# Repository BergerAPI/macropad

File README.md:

# Macropad

This project demonstrates how to build a simple macropad powered by a microcontroller using the same chip as the Raspberry Pi Pico (RP2040).
You can use the files here to 3D print, assemble, and program your own version!

The video of the project was recorded using a custom microcontroller, which is not yet publicly available.
However, you can safely use a Raspberry Pi Pico instead — it uses the same RP2040 chip, so all firmware and pinouts should work with minimal or no changes.

## 3D Model Notice

The included 3D model files are provided as-is.
Before printing, you must adjust them to include proper tolerances (fit clearance) for your printer and switches — otherwise, parts may fit too tightly or loosely.

## Requirements

- Microcontroller: Raspberry Pi Pico (or basically any microcontroller)
- Firmware: Included in this repository
- Switches & Keycaps: Any standard mechanical key switches
- 3D Printer: To print the enclosure and plate (or just order the parts like I did)

Optional:

- EEPROM chip — required for advanced features like changing macros on the fly like with QMK

⚠️ Note: The Raspberry Pi Pico does not have built-in EEPROM, so this functionality will be unavailable unless you add one externally.

## Getting Started 🚀

- Print the enclosure and plate (remember to add tolerances).
Assemble the hardware.
- Flash the firmware to your Pico (instructions in /firmware).
- Connect to your computer and enjoy your new macropad!

## Open Licence
Feel free to play with the provided files and change them to your liking - I even encourage it.

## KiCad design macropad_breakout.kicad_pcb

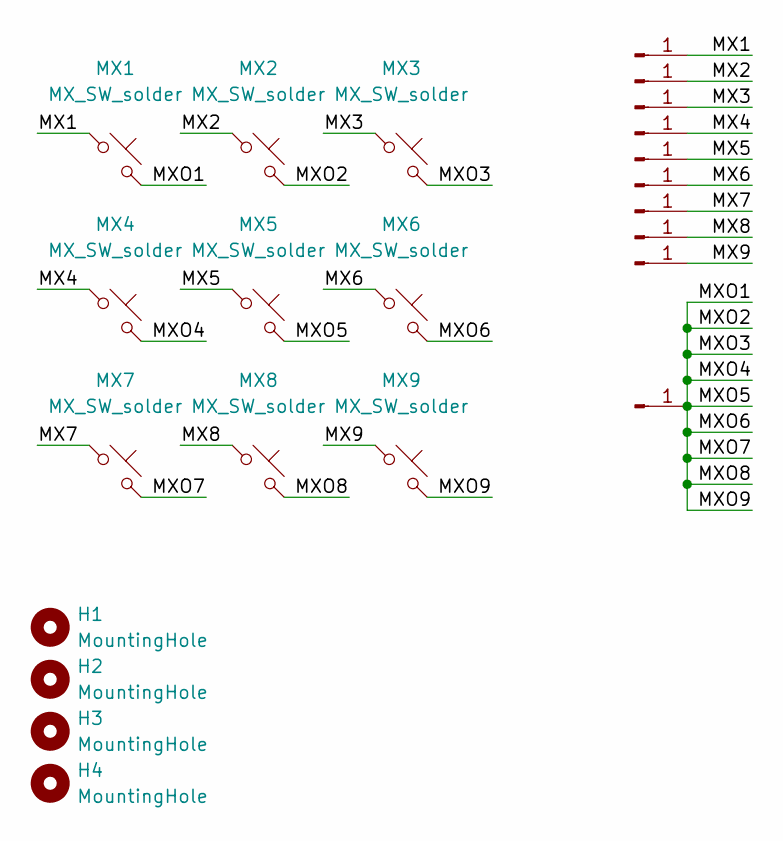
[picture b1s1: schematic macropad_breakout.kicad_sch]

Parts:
H1, H2, H3, H4: MountingHole; MountingHole_3mm
J1, J2, J3, J4, J5, J6, J7, J8, J9, J10: Conn_01x01_Pin; TestPoint_Pad_4.0x4.0mm
MX1, MX2, MX3, MX4, MX5, MX6, MX7, MX8, MX9: MX_SW_solder; SW_MX_1u

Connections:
/MX1: J1.1, MX1.1
/MX2: J2.1, MX2.1
/MX3: J3.1, MX3.1
/MX4: J4.1, MX4.1
/MX5: J5.1, MX5.1
/MX6: J6.1, MX6.1
/MX7: J7.1, MX7.1
/MX8: J8.1, MX8.1
/MX9: J9.1, MX9.1
/MXO1: J10.1, MX1.2, MX2.2, MX3.2, MX4.2, MX5.2, MX6.2, MX7.2, MX8.2, MX9.2

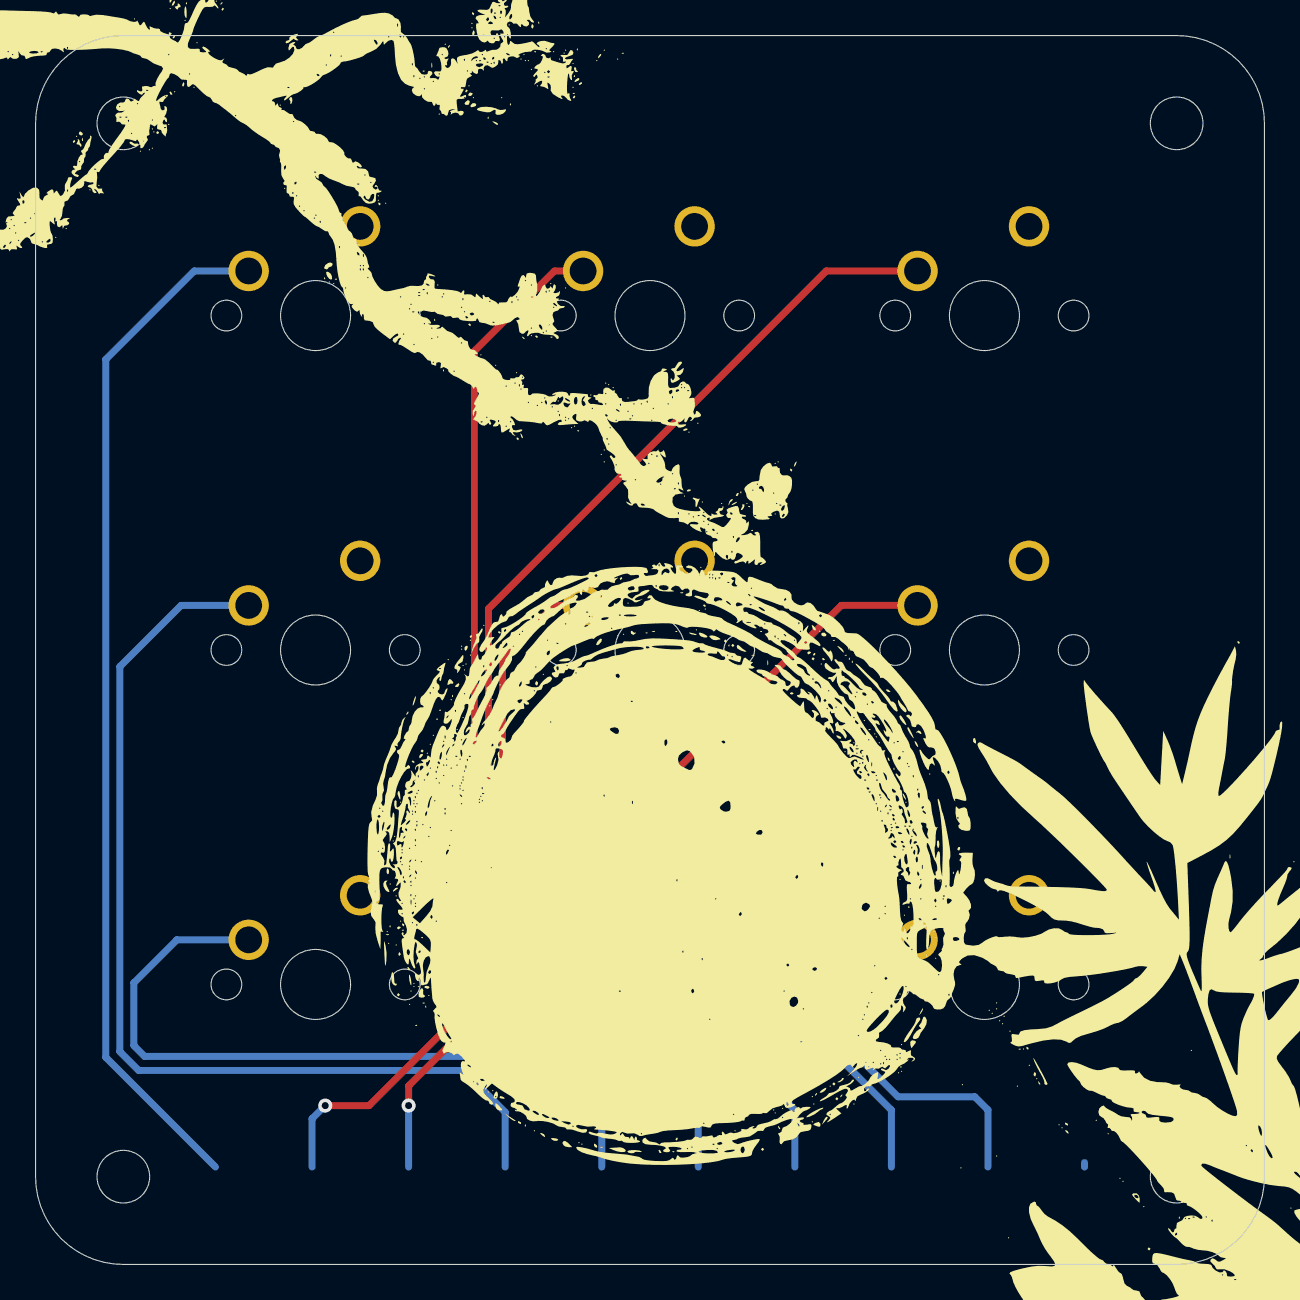
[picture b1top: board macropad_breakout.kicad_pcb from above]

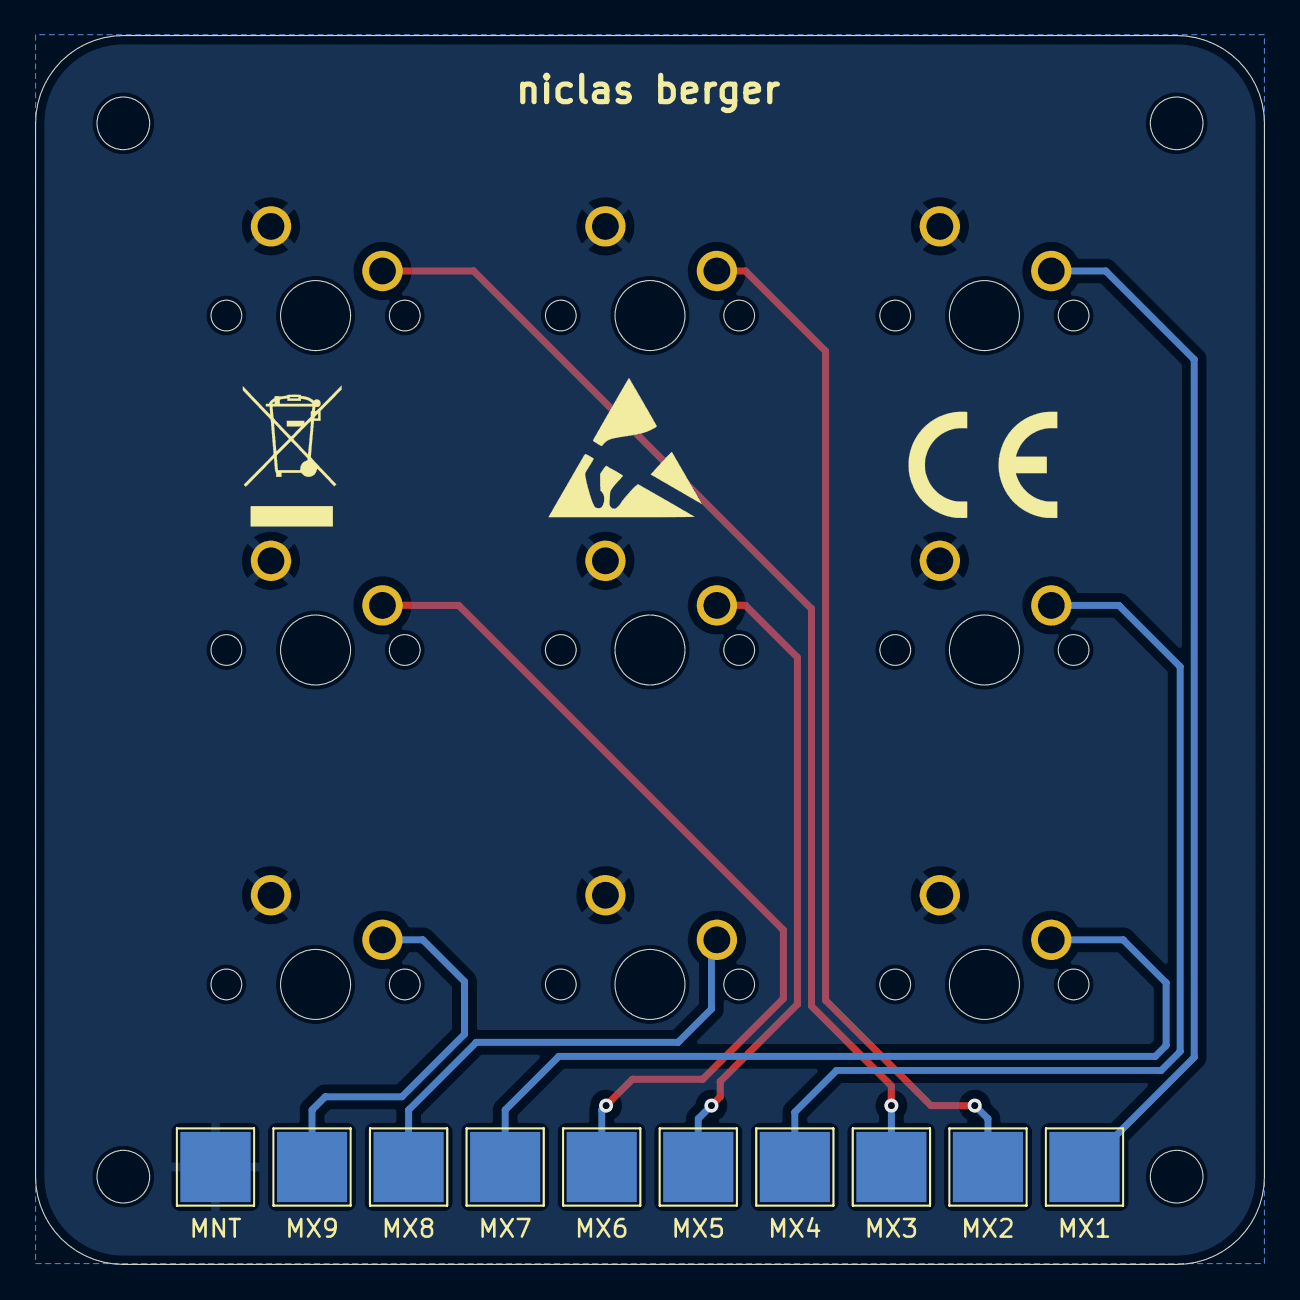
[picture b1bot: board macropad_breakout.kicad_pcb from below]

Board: 2 copper layers, 70.0 x 70.0 mm, 23 parts (10 on the bottom side), 10 nets.

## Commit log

2025-11-08 Added the .step file for the case
2025-11-08 Added the KiCad files for the breakout board
2025-11-08 Update README with project details and instructions
    Added project overview, requirements, and getting started instructions.
